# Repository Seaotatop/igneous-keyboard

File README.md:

# molten-keyboard
 A split, southpaw keyboard with support for rotary encoders and joysticks

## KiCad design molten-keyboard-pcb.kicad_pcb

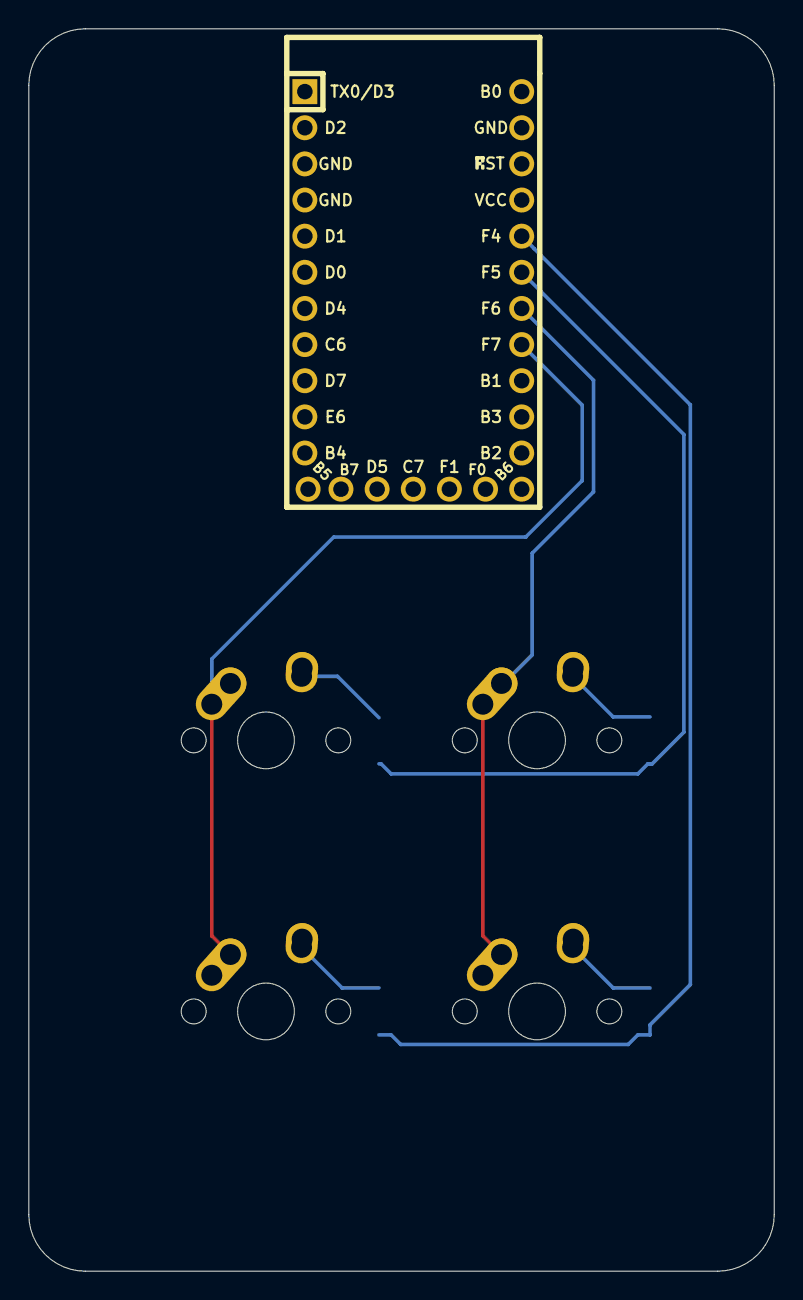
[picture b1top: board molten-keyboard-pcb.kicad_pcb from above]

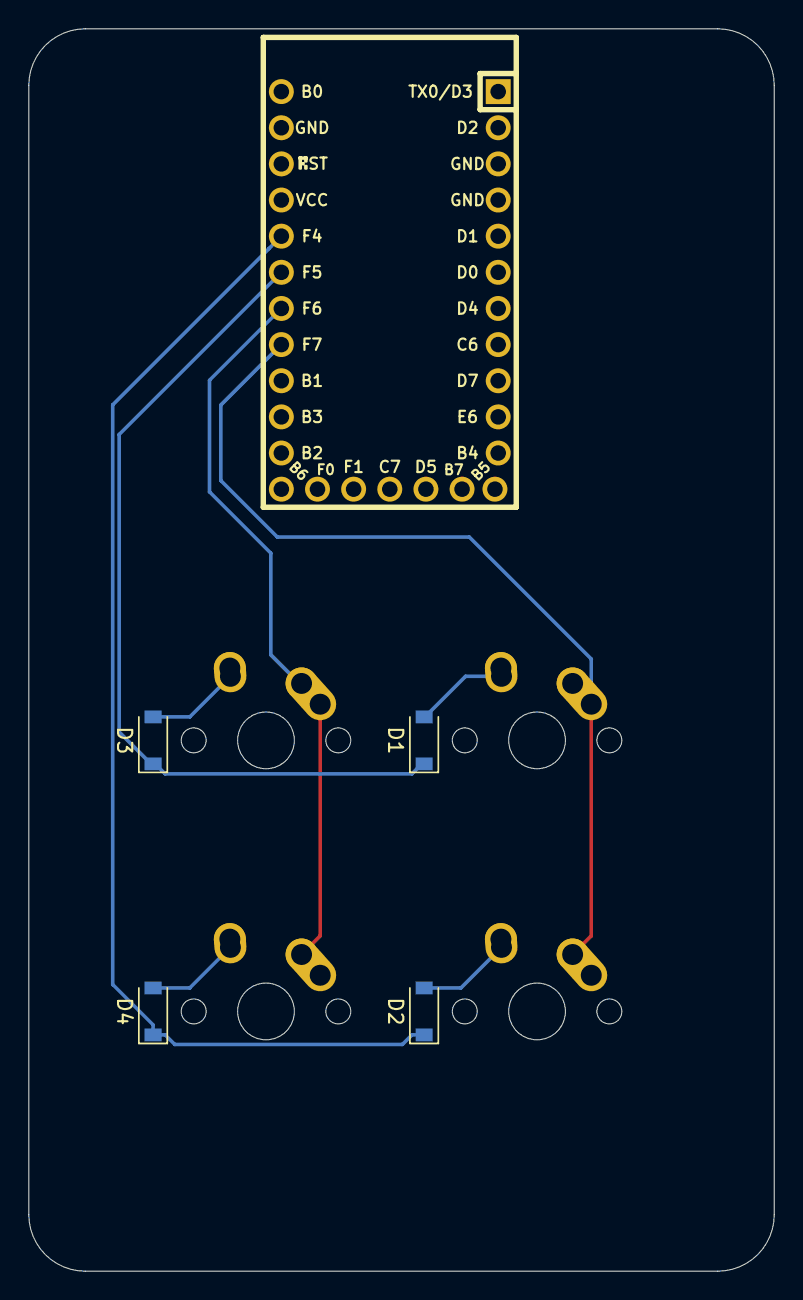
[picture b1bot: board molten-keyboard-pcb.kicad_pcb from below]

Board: 2 copper layers, 52.4 x 87.3 mm, 9 parts (4 on the bottom side), 8 nets.

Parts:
D1, D2, D3, D4: D_Small; D_SOD-123
MX1, MX2, MX3, MX4: MX-NoLED; MX-1U-NoLED
U1: Elite-C

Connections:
COL0: MX1.1, MX2.1, U1.17
COL1: MX3.1, MX4.1, U1.18
unnamed: D1.2, MX1.2
unnamed: D2.2, MX2.2
unnamed: D3.2, MX3.2
unnamed: D4.2, MX4.2
ROW0: D1.1, D3.1, U1.19
ROW1: D2.1, D4.1, U1.20

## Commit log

2021-01-24 Initialize project
    Generated KiCad files
2021-01-24 Add submodules
2021-01-24 Add footprint libraries
2021-01-24 Completed schematic
2021-01-24 Routed tracks
